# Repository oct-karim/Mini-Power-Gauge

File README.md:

<div align="center">

#  USB-C PCB Power Gauge

A simple PCB, functional and efficient. For monitoring current, voltage and power.

</div>

##  Overview

This simple power gauge, controlled by the ATmega328P microcontroller has a voltage range of 0-36V and a current range of 0-3A. 
The footprints have been chosen to be easy to solder. And the components are widely available.

## Features
-**Range** 0/36V & 0/3.5A    
-**16x2 Display**   
-**Sleep Mode**: Consumes less energy after 30s without mesuring voltage    
-**Warning LED**: Inform the user that the mesurements are reaching the max or a activated failsafe    
-**LCD Ping**: checks if the display is alive or faulty connection  
-**AVR Watchdog**: prevents the microcontroller to freeze for more than 2 sec    
-**I2C Failsafe**: checks if the  I2C communication is good to go    
-**Over range Failsafe**: if the mesurements are more than 36V or 3.5A it shuts down the sensor.    

##  Hardware Overview

| Component | Function |
| :--- | :--- |
| **ATmega328p** | Microcontroller handling data and display. |
| **INA226** | I2C current and power sensor. |
| **HY1602E** | Standard 16x2 character LCD display. |
| **PCF8574AT** | I2C expander to drive the LCD using less pins. |
| **USB-C Port** | Power input. |
| **ICSP Socket** | Firmware upload. |

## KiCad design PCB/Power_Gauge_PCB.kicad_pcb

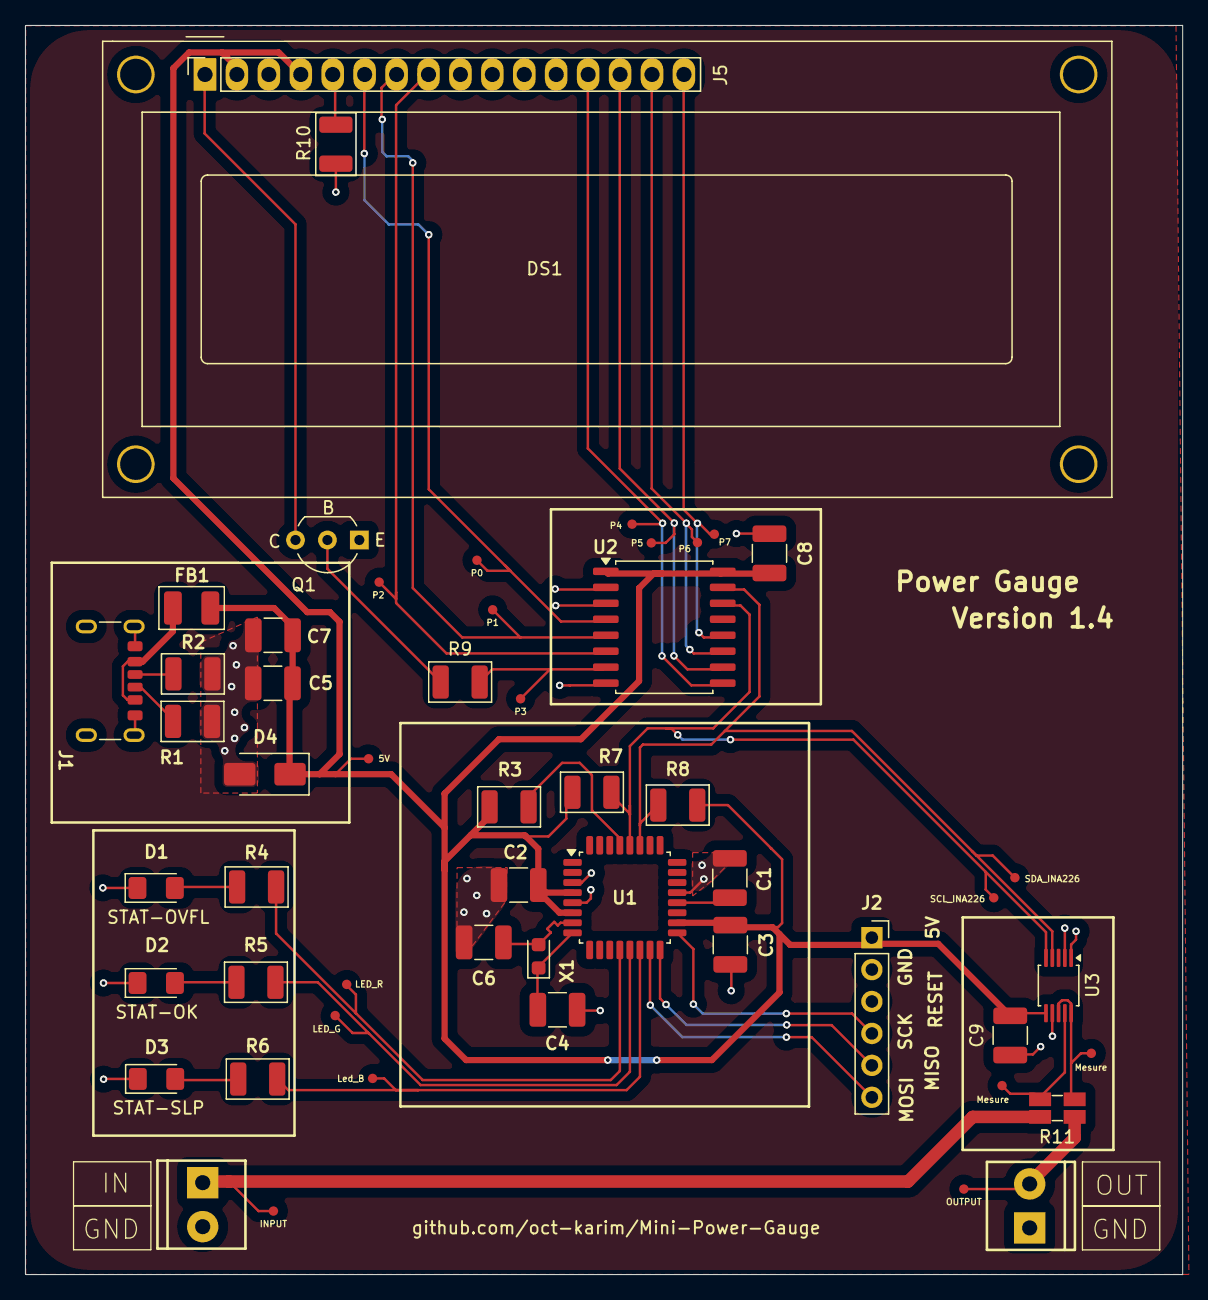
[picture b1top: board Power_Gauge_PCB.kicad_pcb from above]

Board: 2 copper layers, 92.0 x 99.4 mm, 54 parts (0 on the bottom side), 35 nets.

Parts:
C1, C2, C3, C7, C8, C9: 100n; C_1210_3225Metric_Pad1.33x2.70mm_HandSolder
C4, C6: 22p; C_1210_3225Metric_Pad1.33x2.70mm_HandSolder
C5: 10µ; C_1210_3225Metric_Pad1.33x2.70mm_HandSolder
D1: RED; LED_1206_3216Metric_Pad1.42x1.75mm_HandSolder
D2: GREEN; LED_1206_3216Metric_Pad1.42x1.75mm_HandSolder
D3: BLUE; LED_1206_3216Metric_Pad1.42x1.75mm_HandSolder
D4: SMAJ5.0A; D_SMA
DS1: HY1602E; WC1602A
FB1: 300Ω@100MHz; Ferrite_1210_3225Metric_Pad1.42x2.65mm_BigPads
J1: USB_C_Receptacle_PowerOnly_6P; USB_C_Receptacle_GCT_USB4125-xx-x-0190_6P_TopMnt_Horizontal
J2: Conn_01x06_Socket; PinSocket_1x06_P2.54mm_Vertical
J3, J4: 3.5mm; ScrewTerminal_1x02_P3.5mm_Horizontal_Black
J5: Conn_01x16_Socket; PinSocket_1x16_P2.54mm_Vertical
Q1: 2N3904; TO-92_Inline_Wide_EBC
R1, R2: 5.1K; R_1210_3225Metric_Pad1.30x2.65mm
R3: 10k; R_1210_3225Metric_Pad1.30x2.65mm
R4, R5, R6: 470; R_1210_3225Metric_Pad1.30x2.65mm
R7, R8: 4.7k; R_1210_3225Metric_Pad1.30x2.65mm
R9, R10: 1k; R_1210_3225Metric_Pad1.30x2.65mm
R11: 0,02; R_Shunt_Ohmite_LVK12
TP1: LED_R; TestPoint-0.75mm
TP2: LED_G; TestPoint-0.75mm
TP3: Led_B; TestPoint-0.75mm
TP4: SCL_INA226; TestPoint-0.75mm
TP5: SDA_INA226; TestPoint-0.75mm
TP6: 5V; TestPoint-0.75mm
TP7: INPUT; TestPoint-0.75mm
TP8: OUTPUT; TestPoint-0.75mm
TP9: P1; TestPoint-0.75mm
TP10: P3; TestPoint-0.75mm
TP11: P5; TestPoint-0.75mm
TP12: P7; TestPoint-0.75mm
TP13: P0; TestPoint-0.75mm
TP14: P2; TestPoint-0.75mm
TP15: P4; TestPoint-0.75mm
TP16: P6; TestPoint-0.75mm
TP17, TP18: Mesure; TestPoint-0.75mm
U1: ATmega328P-A; TQFP-32_7x7mm_P0.8mm
U2: PCF8574AT; SOIC-16W_7.5x10.3mm_P1.27mm
U3: INA226; VSSOP-10_3x3mm_P0.5mm
X1: 16MHz; Crystal_SMD_2012-2Pin_2.0x1.2mm_HandSoldering

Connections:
5V: C2.2, C3.2, C5.1, C7.2, C8.2, C9.2, D4.1 (A1), DS1.2 (LEDA), DS1.4 (VDD), FB1.2, J2.1, J5.2, J5.4, R3.1, R7.2, R8.2, TP6.1 (1_1), U1.4 (VCC), U1.6 (VCC), U1.18 (AVCC), U2.1 (A0), U2.16 (VDD), U3.6 (VS)
/CONN_DISPLAY1: DS1.5 (Vo), J5.5, R10.2
/CONN_DISPLAY2: DS1.1 (LEDK), J5.1, Q1.3 (C)
GND: C1.1, C2.1, C3.1, C4.1, C5.2, C6.1, C7.1, C8.1, C9.1, D1.1 (K), D2.1 (K), D3.1 (K), D4.2 (A2), DS1.3 (VSS), J1.A12 (GND), J1.B12 (GND), J1.S1 (SHIELD), J2.2, J3.2, J4.1, J5.3, Q1.1 (E), R1.1, R2.2, R10.1, U1.3 (GND), U1.5 (GND), U1.21 (GND), U2.2 (A1), U2.3 (A2), U2.8 (GND), U3.1 (A1), U3.2 (A0), U3.7 (GND)
INPUT: J3.1, R11.1, TP7.1 (1_1)
MISO: J2.5, U1.16 (PB4)
MOSI: J2.6, U1.15 (PB3)
unnamed: D1.2 (A), R4.1
unnamed: D2.2 (A), R5.1
unnamed: D3.2 (A), R6.1
unnamed: FB1.1, J1.A9 (VBUS), J1.B9 (VBUS)
unnamed: J1.A5 (CC1), R2.1
unnamed: J1.B5 (CC2), R1.2
unnamed: Q1.2 (B), R9.1
unnamed: C1.2, U1.20 (AREF)
unnamed: R4.2, TP1.1 (1_1), U1.12 (PB0)
unnamed: R5.2, TP2.1 (1_1), U1.13 (PB1)
unnamed: R6.2, TP3.1 (1_1), U1.14 (PB2)
unnamed: C6.2, U1.7 (XTAL1/PB6), X1.2
unnamed: C4.2, U1.8 (XTAL2/PB7), X1.1
unnamed: R11.3, TP17.1 (1_1), U3.8 (Vbus), U3.10 (Vin+)
unnamed: R11.2, TP18.1 (1_1), U3.9 (Vin-)
OUTPUT: J4.2, R11.4, TP8.1 (1_1)
P0: DS1.6 (RS), J5.6, TP13.1 (1_1), U2.4 (P0)
P1: DS1.7 (R/~W), J5.7, TP9.1 (1_1), U2.5 (P1)
P2: DS1.8 (E), J5.8, TP14.1 (1_1), U2.6 (P2)
P3: R9.2, TP10.1 (1_1), U2.7 (P3)
P4: DS1.13 (DB4), J5.13, TP15.1 (1_1), U2.9 (P4)
P5: DS1.14 (DB5), J5.14, TP11.1 (1_1), U2.10 (P5)
P6: DS1.15 (DB6), J5.15, TP16.1 (1_1), U2.11 (P6)
P7: DS1.16 (DB7), J5.16, TP12.1 (1_1), U2.12 (P7)
RESET: J2.3, R3.2, U1.29 (~RESET/PC6)
SCK: J2.4, U1.17 (PB5)
SCL: R7.1, TP4.1 (1_1), U1.28 (PC5), U2.14 (SCL), U3.5 (SCL)
SDA: R8.1, TP5.1 (1_1), U1.27 (PC4), U2.15 (SDA), U3.4 (SDA)

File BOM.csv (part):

JLCPCB BOM Tool - BOM Matching,,,,,,,,,,,,,,,,,,,,,
BOM name:bom-JLCPCB Assembly Order.xlsx,,,,Download Time:2026-08-21 19:15:24,,,,"* Our matching results are updated in real-time, but stock and prices may change. 
If it's been over 24 hours, please re-match before placing your order.",,,,,,,,,,,,,
PCB Assembled Qty:2,,,,"Est. Total Price:23.5544
(Pre-order parts require a quotation for final pricing.)",,,,,,,,,,,,,,,,,
Your BOM,,,,Matched Parts,,,,,,,Order Information,,,,,,,,,,
Designator,Comment,Footprint,JLCPCB Part #,Matches,Part # ,Manufacturer,Footprint,Description,Category,Warning,JLCPCB Part #,Product link,Source,Lib Type,MOQ,Availability,My Parts(JLCPCB Parts),My Parts(Global sourcing & consigned parts),Rec. Order Qty,Unit Price ($),Total Price ($)
U3,INA226,VSSOP-10_3x3mm_P0.5mm,,Select by System,INA226AIDGSR,Texas Instruments,VSSOP-10_3x3mm_P0.5mm,-40?~+125? 0.1uV/? 0V~36V 100pA 140dB 2.5uV 2.7V~5.5V 330uA High-side detection?Low-side detection?Bidirectional detection?Power monitoring?Digital output interface?Programmable threshold alarm?Enable/shutdown function ±40V VSSOP-10 Current Sense Amplifiers ROHS,Current Sense Amplifiers,,C49851,https://jlcpcb.com/partdetail/TexasInstruments-INA226AIDGSR/C49851,In-stock,Extended,1,44137,0,0,2,"0,9251","1,8502"
U1,ATmega328P-A,TQFP-32_7x7mm_P0.8mm,,Select by Customer,ATMEGA328P-AU,Microchip Tech,TQFP-32_7x7mm_P0.8mm,-40?~+85? 1.8V~5.5V 10bit 1KB 20MHz 23 2KB 32KB 8 Bit AVR Built-in FLASH TQFP-32(7x7) Microcontrollers (MCU/MPU/SOC) ROHS,Microcontrollers (MCU/MPU/SOC),,C14877,https://jlcpcb.com/partdetail/MicrochipTech-ATMEGA328PAU/C14877,In-stock,Extended,1,72884,0,0,2,"2,6308","5,2616"
DS1,HY1602E,HY1602E,,Select by System,HS1602A-B,HS,HY1602E,-20?~+70? 2 55.7x11mm 5V Blue background white text SPLC780 - LCD Screen ROHS,LCD Screen,,C18198249,https://jlcpcb.com/partdetail/HS-HS1602AB/C18198249,In-stock,Extended,1,605,0,0,2,"2,342","4,684"
R11,"0,02",R_Shunt_Ohmite_LVK12,,Select by System,PE1206FRF470R02L,YAGEO,R_Shunt_Ohmite_LVK12,1W 20m? Metal Film Resistor ±1% ±100ppm/? 1206 Current Sense Resistors / Shunt Resistors ROHS,Current Sense Resistors / Shunt Resistors,,C164156,https://jlcpcb.com/partdetail/YAGEO-PE1206FRF470R02L/C164156,In-stock,Extended,1,298,0,0,5,"0,0864","0,432"
J1,USB_C_Receptacle_PowerOnly_6P,USB_C_Receptacle_GCT_USB4125-xx-x-0190_6P_TopMnt_Horizontal,,Select by System,TYPE-C-31-M-17,Korean Hroparts Elec,USB_C_Receptacle_GCT_USB4125-xx-x-0190_6P_TopMnt_Horizontal,"-30?~+80? 1 20V 3,000 Cycles 5A 6.8mm 6P Female Surface Mount, Right Angle Type-C SMD USB Connectors ROHS",USB Connectors,,C283540,https://jlcpcb.com/partdetail/Korean_HropartsElec-TYPE_C_31_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,In-stock,Extended,1,20159,0,0,2,"0,1976","0,3952"
FB1,300?@100MHz,Ferrite_1210_3225Metric_Pad1.42x2.65mm_BigPads,,Select by System,CBG322513U301T,FH (Guangdong Fenghua Advanced Tech),Ferrite_1210_3225Metric_Pad1.42x2.65mm_BigPads,1 300?@100MHz 400mA 400m? ±25% 1210 Ferrite Beads ROHS,Ferrite Beads,,C124095,https://jlcpcb.com/partdetail/125369-CBG322513U301T/C124095,In-stock,Extended,1,1706,0,0,6,"0,0603","0,3618"
J5,Conn_01x06_Socket,PinSocket_1x06_P2.54mm_Vertical,,Select by System,PM2.54-1*6,ZHOURI,PinSocket_1x06_P2.54mm_Vertical,"-40?~+105? 1 1x6P 2.54mm 2.54mm 2.5A 6P 8.5mm Square Hole Through Hole Top ??,P=2.54mm Female Headers ROHS",Female Headers,,C5224026,https://jlcpcb.com/partdetail/ZHOURI-PM2_54_16/C5224026,In-stock,Extended,1,5692,0,0,2,"0,0835","0,167"
J4,Conn_01x16_Socket,PinSocket_1x16_P2.54mm_Vertical,,Select by System,PM200-1-16-Z-4.3,HCTL,PinSocket_1x16_P2.54mm_Vertical,"-40?~+105? 1 1.5A 16P 1x16P 2mm 4.3mm Brass Square Hole Through Hole Top ??,P=2mm Female Headers ROHS",Female Headers,,C3012142,https://jlcpcb.com/partdetail/HCTL-PM200_1_16_Z_43/C3012142,In-stock,Extended,1,160,0,0,2,"0,3089","0,6178"
U2,PCF8574AT,SOIC-16W_7.5x10.3mm_P1.27mm,,Select by System,PCF8574AT/TR,HGSEMI,SOIC-16W_7.5x10.3mm_P1.27mm,-40?~+85? 100kHz 10uA 16 2.5V~6V 25mA 300uA 8 Cascade and address expansion?Built-in LED driver I2C Interrupt Output Quasi-bidirectional output SOP-16-W I/O Expanders ROHS,I/O Expanders,,C2987289,https://jlcpcb.com/partdetail/HGSEMI-PCF8574ATTR/C2987289,In-stock,Extended,1,450,0,0,2,"0,6833","1,3666"
C5,10µ,1210,,Select by System,CL32B106KAJNNNE,Samsung Electro-Mechanics,1210,10uF 25V X7R ±10% 1210 Multilayer Ceramic Capacitors MLCC - SMD/SMT ROHS,Multilayer Ceramic Capacitors MLCC - SMD/SMT,,C39232,https://jlcpcb.com/partdetail/40215-CL32B106KAJNNNE/C39232,In-stock,Extended,1,200000,0,0,6,"0,1304","0,7824"
"R4,R5,R6",470,1210,,Select by System,RC1210JR-07470RL,YAGEO,1210,-55?~+155? 200V 470? 500mW Thick Film Resistor ±100ppm/? ±5% 1210 Chip Resistor - Surface Mount ROHS,Chip Resistor - Surface Mount,,C137072,https://jlcpcb.com/partdetail/YAGEO-RC1210JR07470RL/C137072,In-stock,Extended,1,4148,0,0,16,"0,0173","0,2768"
D3,BLUE,1206,,Unconfirmed,XL-3216UBC,XINGLIGHT,1206,-40?~+85? 120° 20mA 264mcd 3.4V 460nm~475nm 465nm 70mW Blue Discrete Diode Top-mount Water Clear 1206 LED Indication - Discrete ROHS,LED Indication - Discrete,1.The comment (XL-3216UBC) of this part does not match the one (BLUE) provided in your BOM. Please confirm;,C965827,https://jlcpcb.com/partdetail/XINGLIGHT-XL3216UBC/C965827,In-stock,Extended,1,214751,0,0,20,"0,0101","0,202"
"R10,R9",1k,1210,,Unconfirmed,1210W2J0102T5E,UNI-ROYAL(Uniroyal Elec),1210,-55?~+155? 1k? 200V 500mW Thick Film Resistor ±100ppm/? ±5% 1210 Chip Resistor - Surface Mount ROHS,Chip Resistor - Surface Mount,1.The comment (1210W2J0102T5E) of this part does not match the one (1k) provided in your BOM. Please confirm;,C270888,https://jlcpcb.com/partdetail/260268-1210W2J0102T5E/C270888,In-stock,Extended,1,46379,0,0,15,"0,02","0,3"
"C1,C2,C3,C7,C8,C9",100n,1210,,Unconfirmed,1210B104K501CT,Walsin Tech Corp,1210,100nF 500V X7R ±10% 1210 Multilayer Ceramic Capacitors MLCC - SMD/SMT ROHS,Multilayer Ceramic Capacitors MLCC - SMD/SMT,1.The comment (1210B104K501CT) of this part does not match the one (100n) provided in your BOM. Please confirm;,C304008,https://jlcpcb.com/partdetail/Walsin_TechCorp-1210B104K501CT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,In-stock,Extended,1,28329,0,0,16,"0,1588","2,5408"
"R7,R8",4.7k,1210,,Unconfirmed,FRC1210F4701TS,FOJAN,1210,-55?~+155? 200V 4.7k? 500mW Thick Film Resistor ±1% ±100ppm/? 1210 Chip Resistor - Surface Mount ROHS,Chip Resistor - Surface Mount,1.The comment (FRC1210F4701TS) of this part does not match the one (4.7k) provided in your BOM. Please confirm;,C2930443,https://jlcpcb.com/partdetail/FOJAN-FRC1210F4701TS/C2930443,In-stock,Extended,1,58696,0,0,15,"0,0118","0,177"
D2,GREEN,1206,,Unconfirmed,XL-3216UGC-FB,XINGLIGHT,1206,-40?~+85? 120° 20mA 3.4V 515nm~535nm 525nm 70mW 900mcd Discrete Diode Emerald Green Reverse Mount Water Clear 1206 LED Indication - Discrete ROHS,LED Indication - Discrete,1.The comment (XL-3216UGC-FB) of this part does not match the one (GREEN) provided in your BOM. Please confirm;,C3646937,https://jlcpcb.com/partdetail/XINGLIGHT-XL_3216UGCFB/C3646937,In-stock,Extended,1,428094,0,0,15,"0,01","0,15"
Q1,2N3904,TO-92_Inline_Wide_EBC,,Select by System,2N3904,JSMSEMI,TO-92_Inline_Wide_EBC,-55?~+150? 1 NPN 200mA 300 300MHz 300mV 40V 50nA 625mW 6V NPN TO-92 Bipolar (BJT) ROHS,Bipolar (BJT),,C2874602,https://jlcpcb.com/partdetail/JSMSEMI-2N3904/C2874602,In-stock,Extended,1,59164,0,0,4,"0,0121","0,0484"
"J2,J3",3.5mm,ScrewTerminal_1x02_P3.5mm_Horizontal_Black,,Select by System,ST-1157-3.5(H=3.5mm),RI SHENG,ScrewTerminal_1x02_P3.5mm_Horizontal_Black,"-25?~+85? 100,000 cycles 12V 3.5mm 50mA 6.5mm 8.3mm No Round Button SMD(SMT) Tab SPST Surface Mount,Vertical Without Bracket SMD Tactile Switches ROHS",Tactile Switches,,C5349422,https://jlcpcb.com/partdetail/RISHENG-ST_1157_3_5_H_3_5mm/C5349422,In-stock,Extended,1,822,0,0,5,"0,0384","0,192"
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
